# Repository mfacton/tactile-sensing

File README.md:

# Robotic Tactile Sensing with Soft Lattices

MIT Computer Science and Artificial Intelligence Laboratory

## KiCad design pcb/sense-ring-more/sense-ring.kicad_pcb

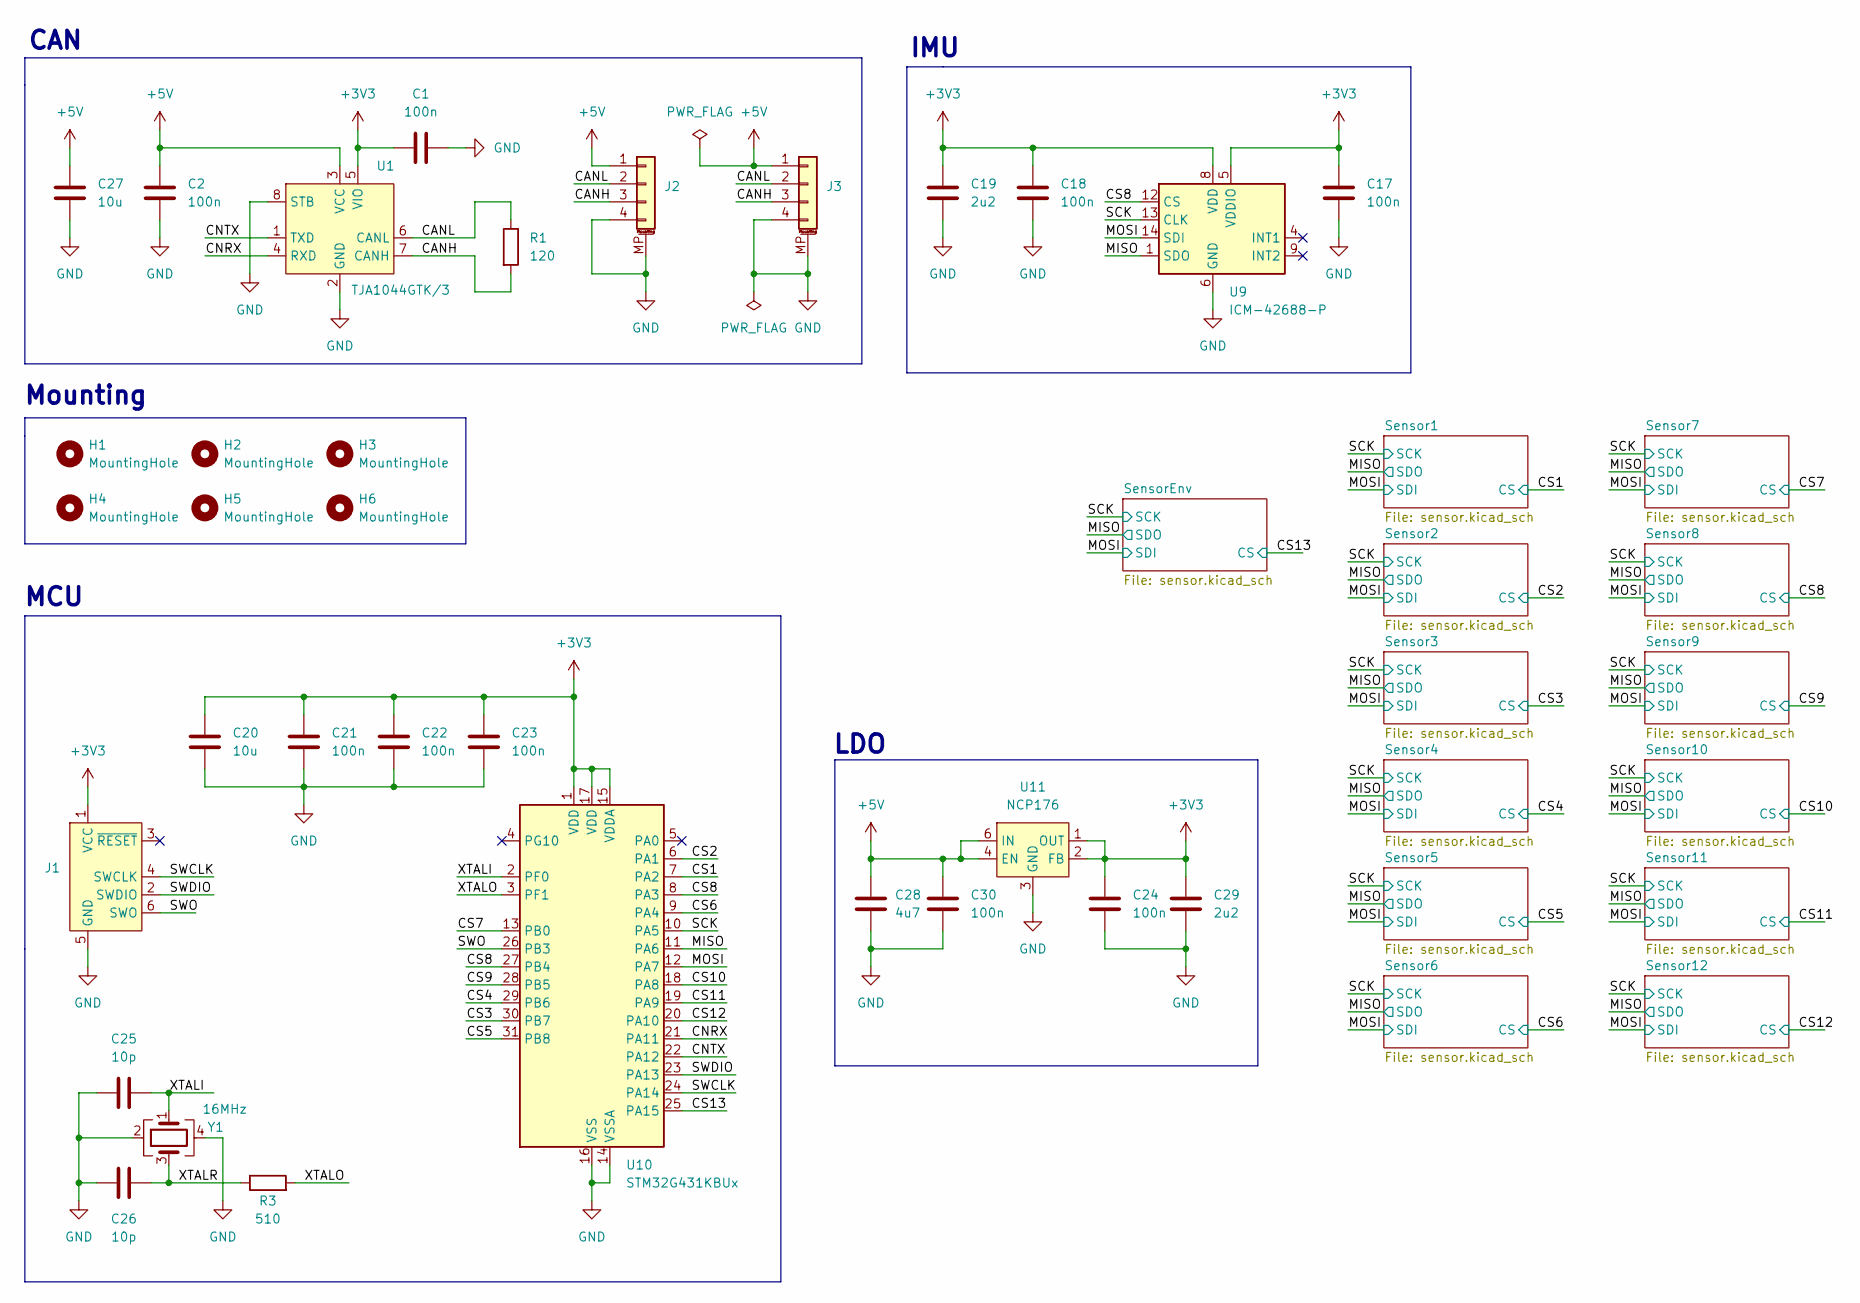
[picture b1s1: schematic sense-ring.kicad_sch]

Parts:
C1, C2, C17, C18, C21, C22, C23, C24, C30: 100n; C_0402_1005Metric; LCSC C1525
C19, C29: 2u2; C_0402_1005Metric; LCSC C12530
C20: 10u; C_0402_1005Metric; LCSC C15525
C25, C26: 10p; C_0402_1005Metric; LCSC C32949
C27: 10u; C_0603_1608Metric; LCSC C19702
C28: 4u7; C_0402_1005Metric; LCSC C23733
H1, H2, H3, H4, H5, H6: MountingHole; MountingHole_3.2mm_M3
J1: Conn_ARM_SWD_TagConnect_TC2030-NL; Tag-Connect_TC2030-IDC-NL_2x03_P1.27mm_Vertical
J2, J3: Conn_01x04_MountingPin; JST_SH_SM04B-SRSS-TB_1x04-1MP_P1.00mm_Horizontal; LCSC C160404
R1: 120; R_1206_3216Metric; LCSC C17909
R3: 510; R_0402_1005Metric; LCSC C25123
U1: TJA1044GTK/3; HVSON-8-1EP_3x3mm_P0.65mm_EP1.6x2.4mm; LCSC C2157795
U9: ICM-42688-P; LGA-14_3x2.5mm_P0.5mm_LayoutBorder3x4y; LCSC C1850418
U10: STM32G431KBUx; QFN-32-1EP_5x5mm_P0.5mm_EP3.45x3.45mm; LCSC C1341901
U11: NCP176; DFN-6-1EP_1.2x1.2mm_P0.4mm_EP0.3x0.94mm_PullBack; LCSC C233363
Y1: 16MHz; Crystal_SMD_3225-4Pin_3.2x2.5mm; LCSC C13738

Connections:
+3V3: C1.1, C17.1, C18.1, C19.1, C20.1, C21.1, C22.1, C23.1, C24.1, C29.1, J1.1 (VCC), U1.5 (VIO), U9.5 (VDDIO), U9.8 (VDD), U10.1 (VDD), U10.15 (VDDA), U10.17 (VDD), U11.1 (OUT), U11.2 (FB); also elsewhere on the board
+5V: C2.2, C27.1, C28.1, C30.1, J2.1, J3.1, U1.3 (VCC), U11.4 (EN), U11.6 (IN)
/CANH: J2.3, J3.3, R1.2, U1.7 (CANH)
/CANL: J2.2, J3.2, R1.1, U1.6 (CANL)
/CNRX: U1.4 (RXD), U10.21 (PA11)
/CNTX: U1.1 (TXD), U10.22 (PA12)
/CS1: U10.7 (PA2); also elsewhere on the board
/CS2: U10.6 (PA1); also elsewhere on the board
/CS3: U10.30 (PB7); also elsewhere on the board
/CS4: U10.29 (PB6); also elsewhere on the board
/CS5: U10.31 (PB8); also elsewhere on the board
/CS6: U10.9 (PA4); also elsewhere on the board
/CS7: U10.13 (PB0); also elsewhere on the board
/CS8: U9.12 (CS), U10.8 (PA3), U10.27 (PB4); also elsewhere on the board
/CS9: U10.28 (PB5); also elsewhere on the board
/CS10: U10.18 (PA8); also elsewhere on the board
/CS11: U10.19 (PA9); also elsewhere on the board
/CS12: U10.20 (PA10); also elsewhere on the board
/CS13: U10.25 (PA15); also elsewhere on the board
/MISO: U9.1 (SDO), U10.11 (PA6); also elsewhere on the board
/MOSI: U9.14 (SDI), U10.12 (PA7); also elsewhere on the board
/SCK: U9.13 (CLK), U10.10 (PA5); also elsewhere on the board
/SWCLK: J1.4 (SWCLK), U10.24 (PA14)
/SWDIO: J1.2 (SWDIO), U10.23 (PA13)
/SWO: J1.6 (SWO), U10.26 (PB3)
/XTALI: C25.2, U10.2 (PF0), Y1.1
/XTALO: R3.2, U10.3 (PF1)
/XTALR: C26.2, R3.1, Y1.3
GND: C1.2, C2.1, C17.2, C18.2, C19.2, C20.2, C21.2, C22.2, C23.2, C24.2, C25.1, C26.1, C27.2, C28.2, C29.2, C30.2, J1.5 (GND), J2.4, J2.MP (MountPin), J3.4, J3.MP (MountPin), U1.2 (GND), U1.8 (STB), U1.9 (EPAD), U9.6 (GND), U9.7 (RESV), U9.11 (RESV), U10.14 (VSSA), U10.16 (VSS), U10.32 (VSS), U10.33 (VSS), U11.3 (GND), U11.7 (EPAD), Y1.2, Y1.4; also elsewhere on the board

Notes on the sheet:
Mounting
LDO
MCU
CAN
IMU

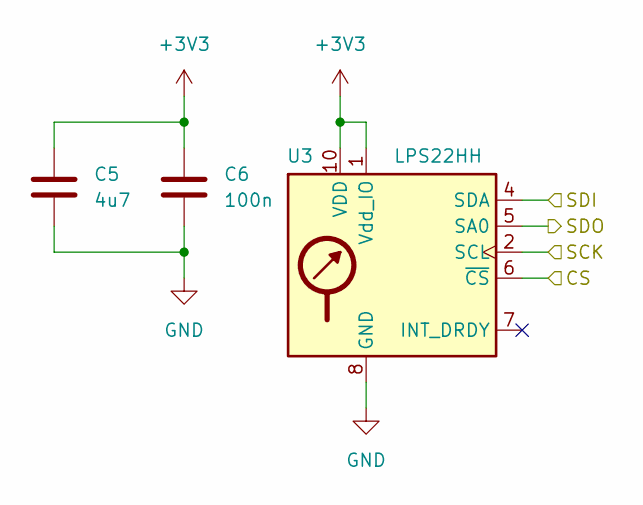
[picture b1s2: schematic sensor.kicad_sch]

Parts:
C5: 4u7; C_0402_1005Metric; LCSC C23733
C6: 100n; C_0402_1005Metric; LCSC C1525
U3: LPS22HH; ST_HLGA-10_2x2mm_P0.5mm_LayoutBorder3x2y; LCSC C2827824

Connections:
+3V3: C5.1, C6.1, U3.1 (Vdd_IO), U3.10 (VDD); also elsewhere on the board
/CS2: U3.6 (~CS); also elsewhere on the board
/MISO: U3.5 (SA0); also elsewhere on the board
/MOSI: U3.4 (SDA); also elsewhere on the board
/SCK: U3.2 (SCL); also elsewhere on the board
GND: C5.2, C6.2, U3.3 (GND), U3.8 (GND), U3.9 (GND); also elsewhere on the board

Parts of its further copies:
C3, C7, C9, C11, C13, C15, C31, C33, C35, C37, C39, C41: 4u7; C_0402_1005Metric; LCSC C23733
C4, C8, C10, C12, C14, C16, C32, C34, C36, C38, C40, C42: 100n; C_0402_1005Metric; LCSC C1525
U2, U4, U5, U6, U7, U8, U12, U13, U14, U15, U16, U17: LPS22HH; ST_HLGA-10_2x2mm_P0.5mm_LayoutBorder3x2y; LCSC C2827824

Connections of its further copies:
+3V3: C3.1, C4.1, C7.1, C8.1, C9.1, C10.1, C11.1, C12.1, C13.1, C14.1, C15.1, C16.1, C31.1, C32.1, C33.1, C34.1, C35.1, C36.1, C37.1, C38.1, C39.1, C40.1, C41.1, C42.1, U2.1 (Vdd_IO), U2.10 (VDD), U4.1 (Vdd_IO), U4.10 (VDD), U5.1 (Vdd_IO), U5.10 (VDD), U6.1 (Vdd_IO), U6.10 (VDD), U7.1 (Vdd_IO), U7.10 (VDD), U8.1 (Vdd_IO), U8.10 (VDD), U12.1 (Vdd_IO), U12.10 (VDD), U13.1 (Vdd_IO), U13.10 (VDD), U14.1 (Vdd_IO), U14.10 (VDD), U15.1 (Vdd_IO), U15.10 (VDD), U16.1 (Vdd_IO), U16.10 (VDD), U17.1 (Vdd_IO), U17.10 (VDD); also elsewhere on the board
/CS1: U2.6 (~CS); also elsewhere on the board
/CS3: U4.6 (~CS); also elsewhere on the board
/CS4: U5.6 (~CS); also elsewhere on the board
/CS5: U6.6 (~CS); also elsewhere on the board
/CS6: U8.6 (~CS); also elsewhere on the board
/CS7: U12.6 (~CS); also elsewhere on the board
/CS8: U13.6 (~CS); also elsewhere on the board
/CS9: U14.6 (~CS); also elsewhere on the board
/CS10: U15.6 (~CS); also elsewhere on the board
/CS11: U16.6 (~CS); also elsewhere on the board
/CS12: U17.6 (~CS); also elsewhere on the board
/CS13: U7.6 (~CS); also elsewhere on the board
/MISO: U2.5 (SA0), U4.5 (SA0), U5.5 (SA0), U6.5 (SA0), U7.5 (SA0), U8.5 (SA0), U12.5 (SA0), U13.5 (SA0), U14.5 (SA0), U15.5 (SA0), U16.5 (SA0), U17.5 (SA0); also elsewhere on the board
/MOSI: U2.4 (SDA), U4.4 (SDA), U5.4 (SDA), U6.4 (SDA), U7.4 (SDA), U8.4 (SDA), U12.4 (SDA), U13.4 (SDA), U14.4 (SDA), U15.4 (SDA), U16.4 (SDA), U17.4 (SDA); also elsewhere on the board
/SCK: U2.2 (SCL), U4.2 (SCL), U5.2 (SCL), U6.2 (SCL), U7.2 (SCL), U8.2 (SCL), U12.2 (SCL), U13.2 (SCL), U14.2 (SCL), U15.2 (SCL), U16.2 (SCL), U17.2 (SCL); also elsewhere on the board
GND: C3.2, C4.2, C7.2, C8.2, C9.2, C10.2, C11.2, C12.2, C13.2, C14.2, C15.2, C16.2, C31.2, C32.2, C33.2, C34.2, C35.2, C36.2, C37.2, C38.2, C39.2, C40.2, C41.2, C42.2, U2.3 (GND), U2.8 (GND), U2.9 (GND), U4.3 (GND), U4.8 (GND), U4.9 (GND), U5.3 (GND), U5.8 (GND), U5.9 (GND), U6.3 (GND), U6.8 (GND), U6.9 (GND), U7.3 (GND), U7.8 (GND), U7.9 (GND), U8.3 (GND), U8.8 (GND), U8.9 (GND), U12.3 (GND), U12.8 (GND), U12.9 (GND), U13.3 (GND), U13.8 (GND), U13.9 (GND), U14.3 (GND), U14.8 (GND), U14.9 (GND), U15.3 (GND), U15.8 (GND), U15.9 (GND), U16.3 (GND), U16.8 (GND), U16.9 (GND), U17.3 (GND), U17.8 (GND), U17.9 (GND); also elsewhere on the board

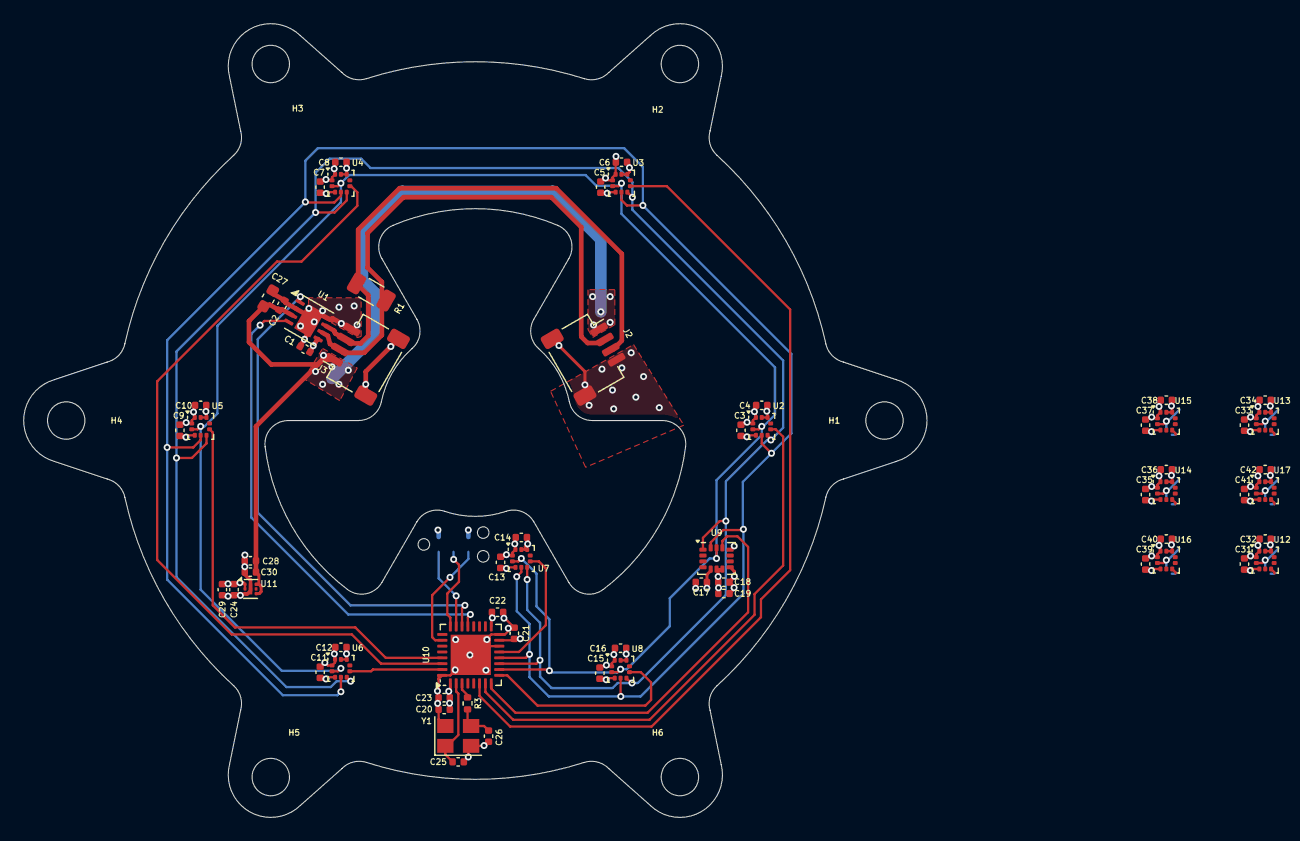
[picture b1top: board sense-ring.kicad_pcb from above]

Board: 4 copper layers, 77.3 x 67.9 mm, 71 parts (1 on the bottom side), 29 nets.

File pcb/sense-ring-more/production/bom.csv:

Designator,Footprint,Quantity,Value,LCSC Part #
"C1, C10, C12, C14, C16, C17, C18, C2, C21, C22, C23, C24, C30, C4, C6, C8",0402,16,100n,C1525
"C11, C13, C15, C28, C3, C5, C7, C9",0402,8,4u7,C23733
"C19, C29",0402,2,2u2,C12530
C20,0402,1,10u,C15525
"C25, C26",0402,2,10p,C32949
C27,0603,1,10u,C19702
"J2, J3",JST_SH_SM04B-SRSS-TB_1x04-1MP_P1.00mm_Horizontal,2,Conn_01x04_MountingPin,C160404
R1,1206,1,120,C17909
R3,0402,1,510,C25123
U1,HVSON-8-1EP_3x3mm_P0.65mm_EP1.6x2.4mm,1,TJA1044GTK/3,C2157795
U10,QFN-32-1EP_5x5mm_P0.5mm_EP3.45x3.45mm,1,STM32G431KBUx,C1341901
U11,DFN-6-1EP_1.2x1.2mm_P0.4mm_EP0.3x0.94mm_PullBack,1,NCP176,C233363
"U2, U3, U4, U5, U6, U7, U8",ST_HLGA-10_2x2mm_P0.5mm_LayoutBorder3x2y,7,LPS22HH,C2827824
U9,LGA-14_3x2.5mm_P0.5mm_LayoutBorder3x4y,1,ICM-42688-P,C1850418
Y1,Crystal_SMD_3225-4Pin_3.2x2.5mm,1,16MHz,C13738

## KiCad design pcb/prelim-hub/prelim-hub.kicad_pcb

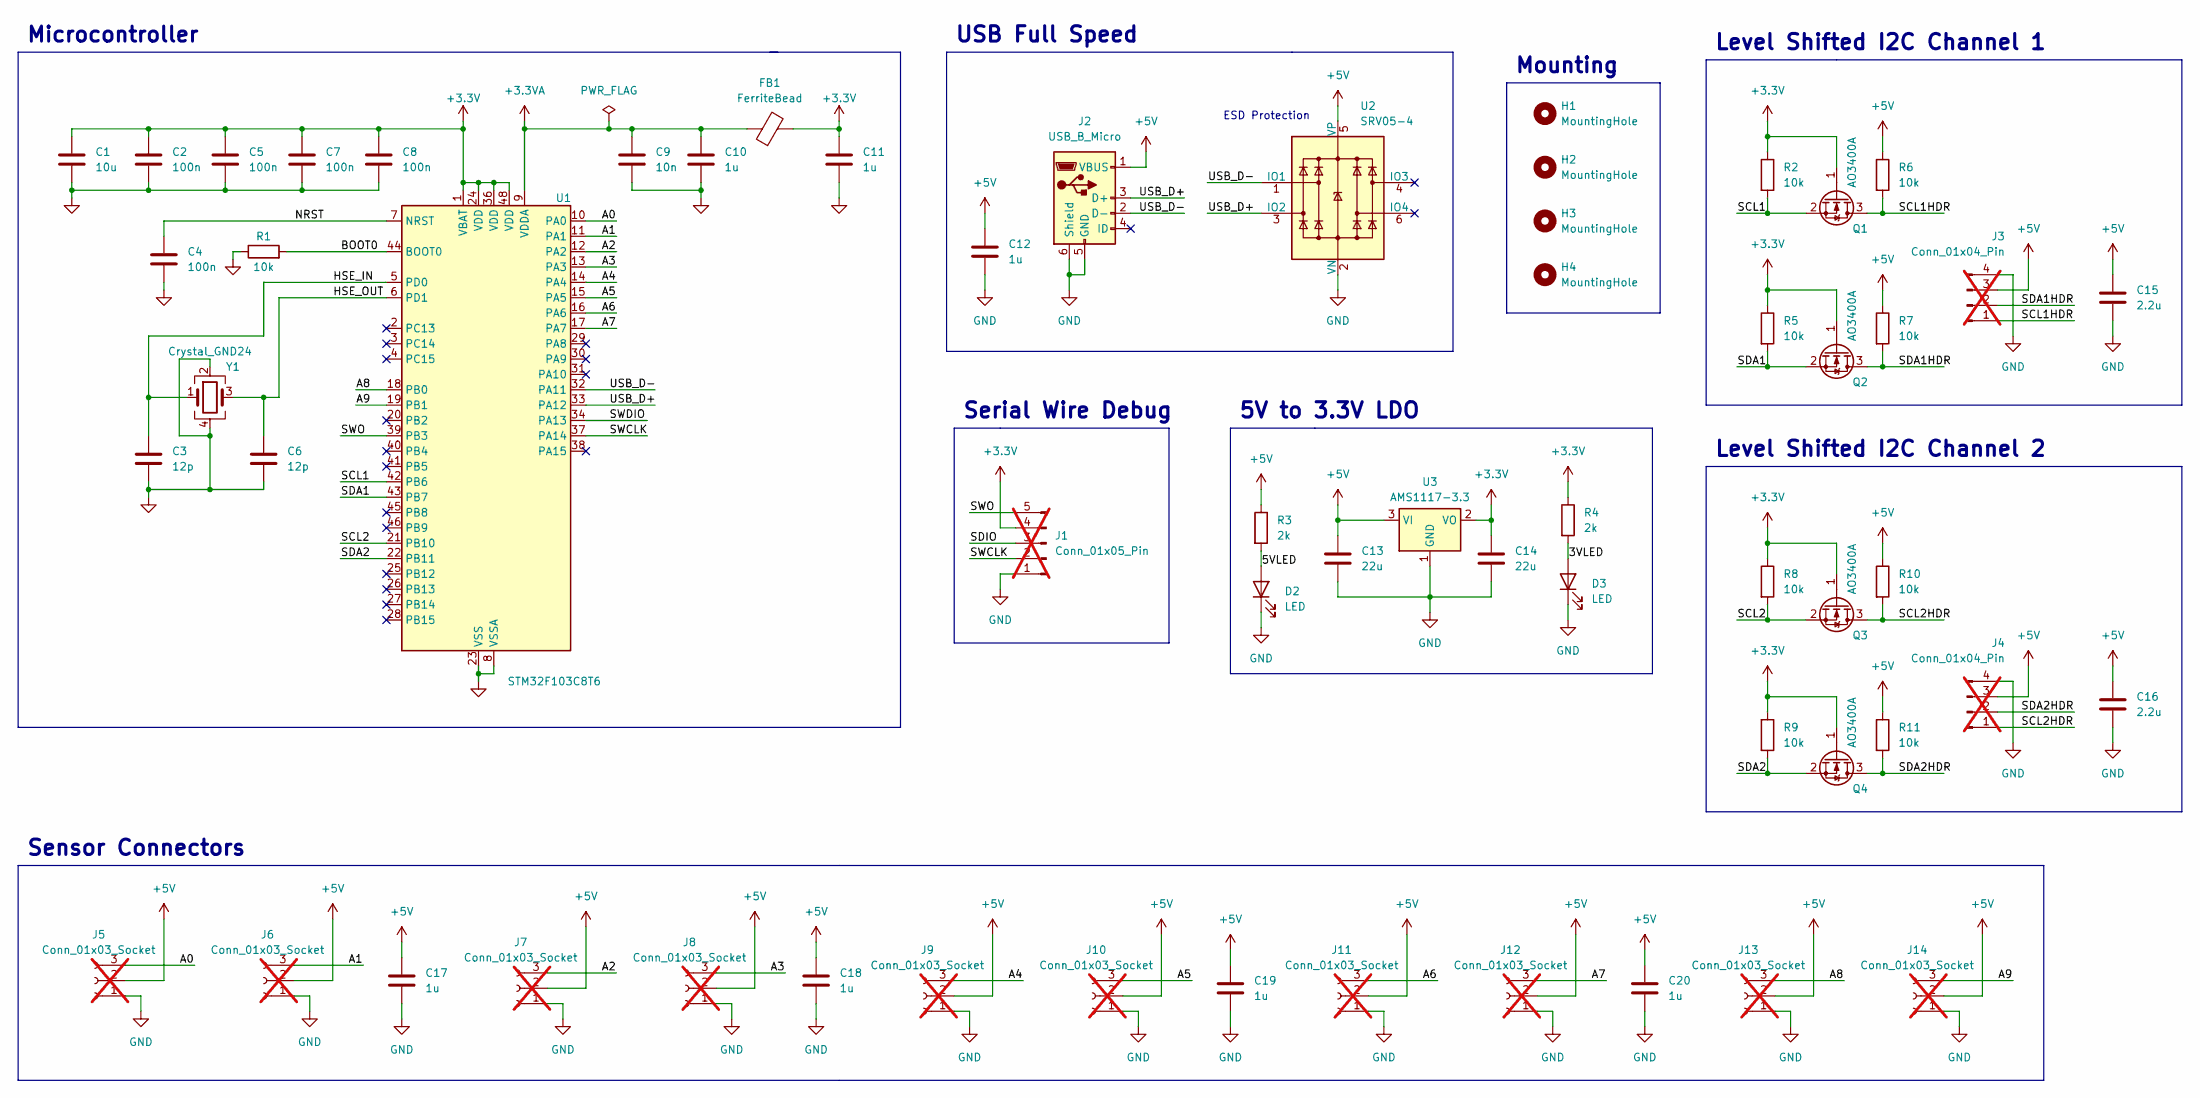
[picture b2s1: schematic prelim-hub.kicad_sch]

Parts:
C1: 10u; C_0603_1608Metric
C2, C4, C5, C7, C8: 100n; C_0402_1005Metric
C3, C6: 12p; C_0402_1005Metric
C9: 10n; C_0402_1005Metric
C10, C11, C12, C17, C18, C19, C20: 1u; C_0402_1005Metric
C13, C14: 22u; C_0805_2012Metric
C15, C16: 2.2u; C_0603_1608Metric
D2, D3: LED; LED_0603_1608Metric
FB1: FerriteBead; L_0805_2012Metric
H1, H2, H3, H4: MountingHole; MountingHole_3.2mm_M3
J1: Conn_01x05_Pin; Conn_Header_P5-2.54; not fitted
J2: USB_B_Micro; USB_Micro-B_Molex-105017-0001
J3, J4: Conn_01x04_Pin; Conn_JST_P4-2.54mm; not fitted
J5, J6, J7, J8, J9, J10, J11, J12, J13, J14: Conn_01x03_Socket; Conn_JST_P3-2.54; not fitted
Q1, Q2, Q3, Q4: AO3400A; SOT-23
R1, R2, R5, R6, R7, R8, R9, R10, R11: 10k; R_0402_1005Metric
R3, R4: 2k; R_0402_1005Metric
U1: STM32F103C8T6; LQFP-48_7x7mm_P0.5mm; LCSC C8734
U2: SRV05-4; SOT-23-6; LCSC C7420376
U3: AMS1117-3.3; SOT-223-3_TabPin2
Y1: Crystal_GND24; Crystal_SMD_3225-4Pin_3.2x2.5mm; LCSC C13738

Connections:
+3.3V: C1.1, C2.1, C5.1, C7.1, C8.1, C11.1, C14.1, FB1.2, J1.4, Q1.1 (G), Q2.1 (G), Q3.1 (G), Q4.1 (G), R2.1, R4.1, R5.1, R8.1, R9.1, U1.1 (VBAT), U1.24 (VDD), U1.36 (VDD), U1.48 (VDD), U3.2 (VO)
+3.3VA: C9.1, C10.1, FB1.1, U1.9 (VDDA)
+5V: C12.1, C13.1, C15.1, C16.1, C17.1, C18.1, C19.1, C20.1, J2.1 (VBUS), J3.3, J4.3, J5.2, J6.2, J7.2, J8.2, J9.2, J10.2, J11.2, J12.2, J13.2, J14.2, R3.1, R6.1, R7.1, R10.1, R11.1, U2.5 (VP), U3.3 (VI)
/3VLED: D3.2 (A), R4.2
/5VLED: D2.2 (A), R3.2
/A0: J5.3, U1.10 (PA0)
/A1: J6.3, U1.11 (PA1)
/A2: J7.3, U1.12 (PA2)
/A3: J8.3, U1.13 (PA3)
/A4: J9.3, U1.14 (PA4)
/A5: J10.3, U1.15 (PA5)
/A6: J11.3, U1.16 (PA6)
/A7: J12.3, U1.17 (PA7)
/A8: J13.3, U1.18 (PB0)
/A9: J14.3, U1.19 (PB1)
/BOOT0: R1.2, U1.44 (BOOT0)
/HSE_IN: C3.1, U1.5 (PD0), Y1.1
/HSE_OUT: C6.1, U1.6 (PD1), Y1.3
/NRST: C4.1, U1.7 (NRST)
/SCL1: Q1.2 (S), R2.2, U1.42 (PB6)
/SCL1HDR: J3.1, Q1.3 (D), R6.2
/SCL2: Q3.2 (S), R8.2, U1.21 (PB10)
/SCL2HDR: J4.1, Q3.3 (D), R10.2
/SDA1: Q2.2 (S), R5.2, U1.43 (PB7)
/SDA1HDR: J3.2, Q2.3 (D), R7.2
/SDA2: Q4.2 (S), R9.2, U1.22 (PB11)
/SDA2HDR: J4.2, Q4.3 (D), R11.2
/SDIO: J1.3
/SWCLK: J1.2, U1.37 (PA14)
/SWDIO: U1.34 (PA13)
/SWO: J1.5, U1.39 (PB3)
/USB_D+: J2.3 (D+), U1.33 (PA12), U2.3 (IO2)
/USB_D-: J2.2 (D-), U1.32 (PA11), U2.1 (IO1)
GND: C1.2, C2.2, C3.2, C4.2, C5.2, C6.2, C7.2, C8.2, C9.2, C10.2, C11.2, C12.2, C13.2, C14.2, C15.2, C16.2, C17.2, C18.2, C19.2, C20.2, D2.1 (K), D3.1 (K), J1.1, J2.5 (GND), J2.6 (Shield), J3.4, J4.4, J5.1, J6.1, J7.1, J8.1, J9.1, J10.1, J11.1, J12.1, J13.1, J14.1, R1.1, U1.8 (VSSA), U1.23 (VSS), U1.35 (VSS), U1.47 (VSS), U2.2 (VN), U3.1 (GND), Y1.2, Y1.4

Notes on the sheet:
Mounting
Level Shifted I2C Channel 1
Microcontroller
5V to 3.3V LDO
Sensor Connectors
USB Full Speed
ESD Protection
Serial Wire Debug
Level Shifted I2C Channel 2

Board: 2 copper layers, 60 parts (0 on the bottom side), 32 nets, no tracks yet.

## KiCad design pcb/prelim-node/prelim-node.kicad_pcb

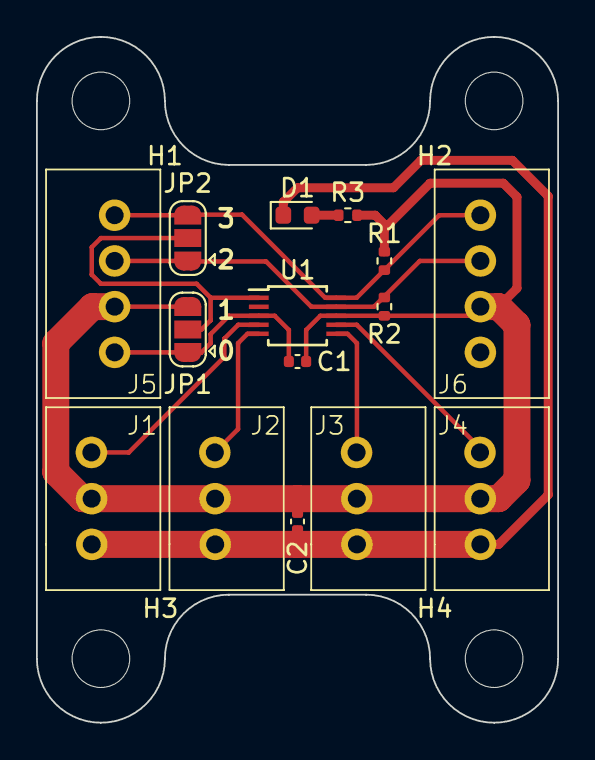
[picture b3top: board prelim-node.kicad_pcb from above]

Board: 2 copper layers, 29.0 x 38.1 mm, 19 parts (0 on the bottom side), 10 nets.

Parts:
C1: 100n; C_0402_1005Metric
C2: 1u; C_0402_1005Metric
D1: LED; LED_0603_1608Metric
H1, H2, H3, H4: MountingHole; MountingHole_3.2mm_M3
J1, J2, J3, J4: Conn_01x03_Socket; Conn_JST_P3-2.54
J5, J6: Conn_01x04_Pin; Conn_JST_P4-2.54mm
JP1, JP2: SolderJumper_3_Open; SolderJumper-3_P1.3mm_Open_RoundedPad1.0x1.5mm
R1, R2: 10k; R_0402_1005Metric
R3: 2k; R_0402_1005Metric
U1: ADS1115IDGS; TSSOP-10_3x3mm_P0.5mm

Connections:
+5V: C1.1, C2.1, J1.2, J2.2, J3.2, J4.2, J5.3, J6.2, JP1.3 (B), R1.1, R2.1, R3.1, U1.8 (VDD)
/5VLED: D1.2 (A), R3.2
/A1: J1.3, U1.4 (AIN0)
/A2: J2.3, U1.5 (AIN1)
/A3: J3.3, U1.6 (AIN2)
/A4: J4.3, U1.7 (AIN3)
/ADDR: JP1.2 (C), JP2.2 (C), U1.1 (ADDR)
/SCL: J5.1, J6.4, JP2.3 (B), R1.2, U1.10 (SCL)
/SDA: J5.2, J6.3, JP2.1 (A), R2.2, U1.9 (SDA)
GND: C1.2, C2.2, D1.1 (K), J1.1, J2.1, J3.1, J4.1, J5.4, J6.1, JP1.1 (A), U1.3 (GND)

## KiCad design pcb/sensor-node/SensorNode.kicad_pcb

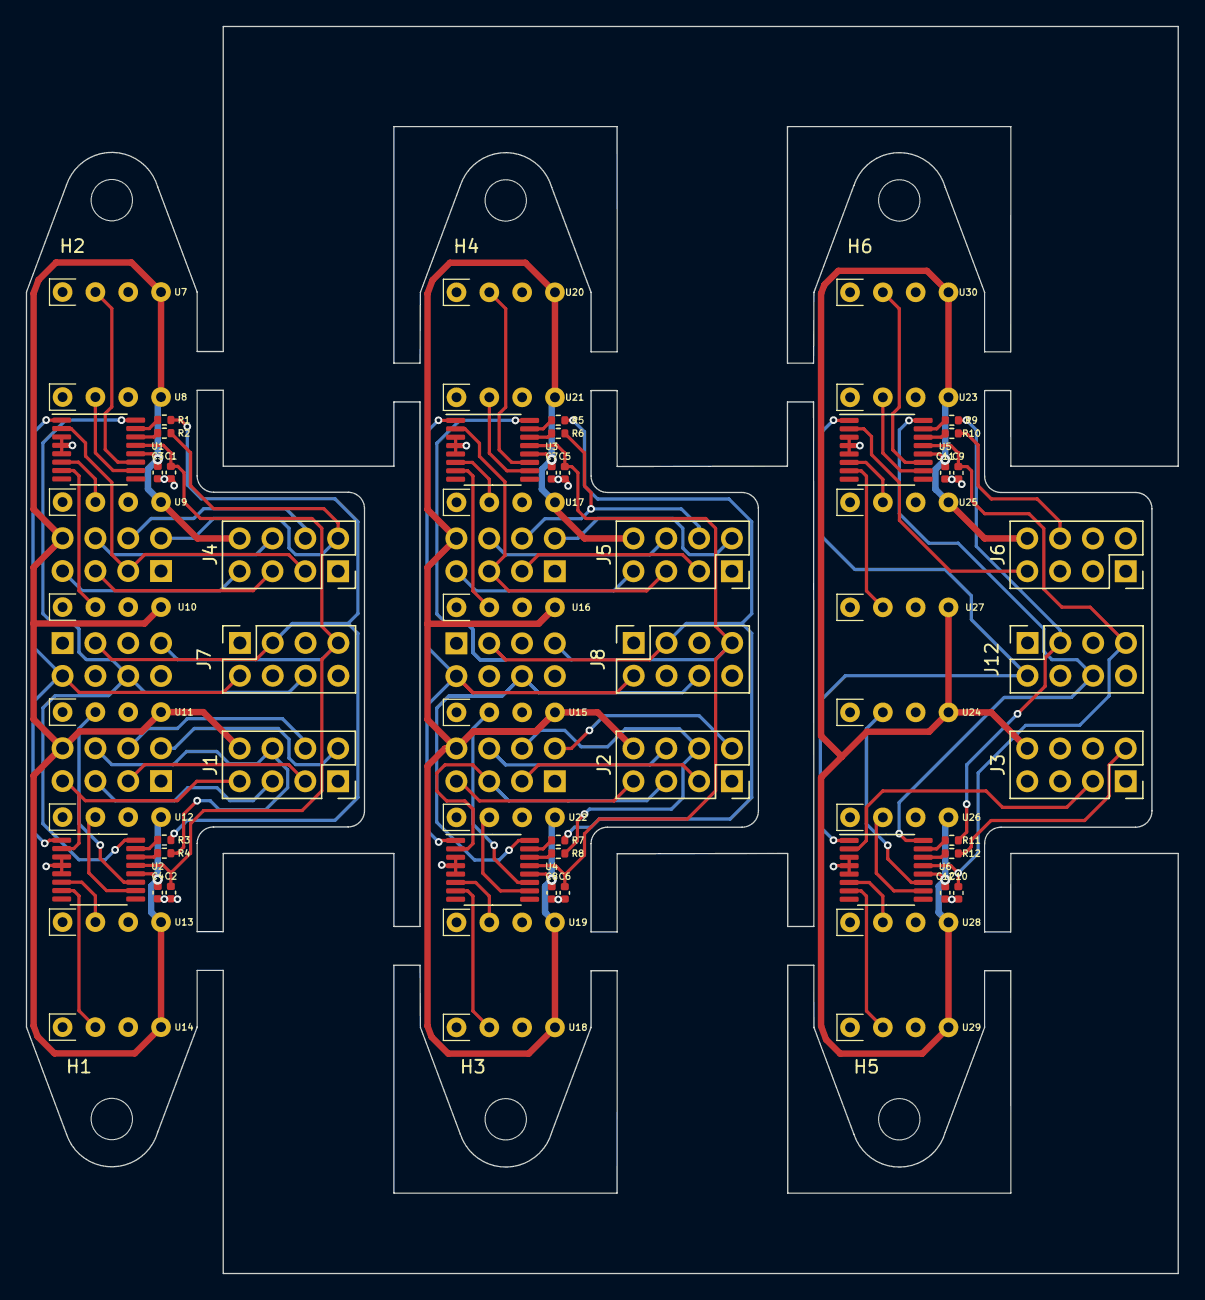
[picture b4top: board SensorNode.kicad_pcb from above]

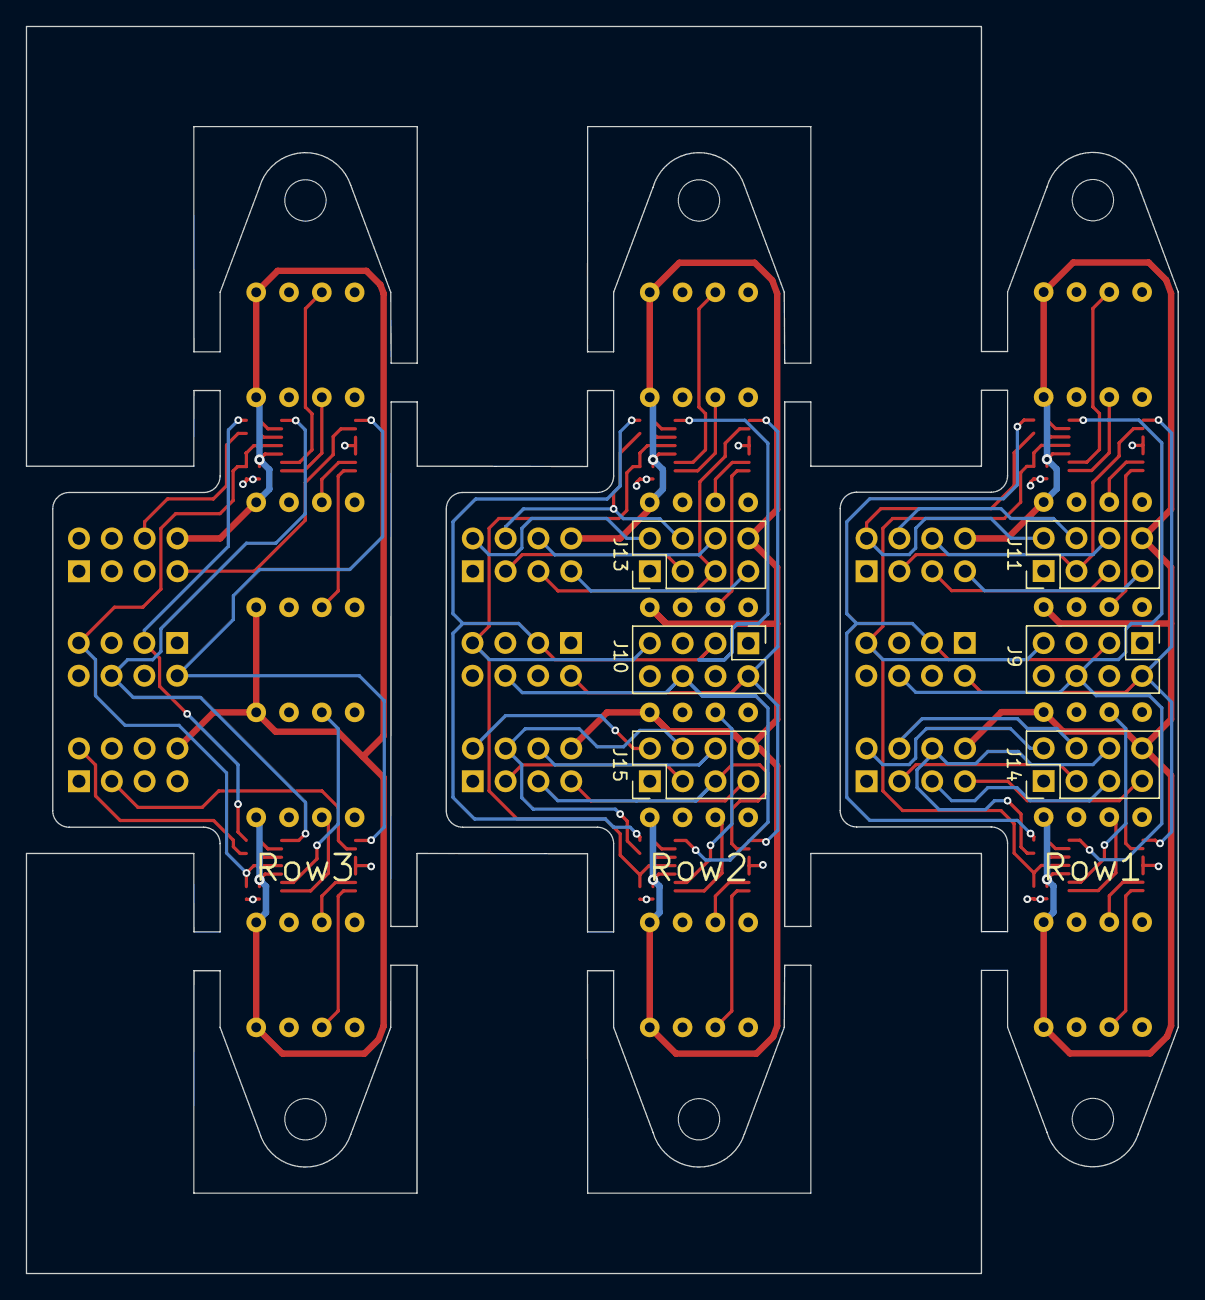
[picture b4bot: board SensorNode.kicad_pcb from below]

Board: 4 copper layers, 89.1 x 96.5 mm, 75 parts (6 on the bottom side), 76 nets.

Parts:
C1, C2, C3, C4, C5, C6, C7, C8, C9, C10, C11, C12: 100n; C_0402_1005Metric
H1, H2, H3, H4, H5, H6: MountingHole; MountingHole_3.2mm_M3
J1, J2, J3, J4, J5, J6, J7, J8, J12: Conn_02x04_Odd_Even; PinSocket_2x04_P2.54mm_Vertical
J9, J10, J11, J13, J14, J15: Conn_02x04_Odd_Even; PinHeader_2x04_P2.54mm_Vertical
R1, R2, R3, R4, R5, R6, R7, R8, R9, R10, R11, R12: 22; R_0402_1005Metric
U1, U2, U3, U4, U5, U6: ADS1220xPW; TSSOP-16_4.4x5mm_P0.65mm
U7, U8, U9, U10, U11, U12, U13, U14, U15, U16, U17, U18, U19, U20, U21, U22, U23, U24, U25, U26, U27, U28, U29, U30: P4V-MINI

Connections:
+3.3V: C1.1, C2.1, C5.1, C6.1, C9.1, C10.1, J7.7, J8.7, J9.7, J10.7, J12.7, U1.13 (DVDD), U2.13 (DVDD), U3.13 (DVDD), U4.13 (DVDD), U5.13 (DVDD), U6.13 (DVDD)
+5V: C3.1, C4.1, C7.1, C8.1, C11.1, C12.1, J1.8, J2.8, J3.8, J4.8, J5.8, J6.8, J11.8, J13.8, J14.8, J15.8, U1.12 (AVDD), U2.12 (AVDD), U3.12 (AVDD), U4.12 (AVDD), U5.12 (AVDD), U6.12 (AVDD), U7.1 (VCC), U8.1 (VCC), U9.1 (VCC), U10.1 (VCC), U11.1 (VCC), U12.1 (VCC), U13.1 (VCC), U14.1 (VCC), U15.1 (VCC), U16.1 (VCC), U17.1 (VCC), U18.1 (VCC), U19.1 (VCC), U20.1 (VCC), U21.1 (VCC), U22.1 (VCC), U23.1 (VCC), U24.1 (VCC), U25.1 (VCC), U26.1 (VCC), U27.1 (VCC), U28.1 (VCC), U29.1 (VCC), U30.1 (VCC)
/CSA1: J4.3, J11.3, U1.2 (~CS)
/CSA2: J4.5, J11.5
/CSA3: J4.7, J11.7
/CSA4: J1.3, J14.3
/CSA5: J1.5, J14.5
/CSA6: J1.7, J14.7, U2.2 (~CS)
/CSB1: J5.3, J13.3
/CSB2: J5.5, J13.5, U3.2 (~CS)
/CSB3: J5.7, J13.7
/CSB4: J2.3, J15.3
/CSB5: J2.5, J15.5, U4.2 (~CS)
/CSB6: J2.7, J15.7
/CSC3: J6.7, U5.2 (~CS)
/CSC4: J3.3, U6.2 (~CS)
/ConnectorIn1/MISO: J7.3, J9.3, R1.2, R3.2
/ConnectorIn1/MOSI: J7.6, J9.6, U1.16 (DIN), U2.16 (DIN)
/ConnectorIn1/SCK: J7.2, J9.2, U1.1 (SCLK), U2.1 (SCLK)
/ConnectorIn2/MISO: J8.3, J10.3, R5.2, R7.2
/ConnectorIn2/MOSI: J8.6, J10.6, U3.16 (DIN), U4.16 (DIN)
/ConnectorIn2/SCK: J8.2, J10.2, U3.1 (SCLK), U4.1 (SCLK)
/ConnectorIn3/MISO: J12.3, R9.2, R11.2
/ConnectorIn3/MOSI: J12.6, U5.16 (DIN), U6.16 (DIN)
/ConnectorIn3/SCK: J12.2, U5.1 (SCLK), U6.1 (SCLK)
/DRA1: J4.2, J11.2, R2.2
/DRA2: J4.4, J11.4
/DRA3: J4.6, J11.6
/DRA4: J1.2, J14.2
/DRA5: J1.4, J14.4
/DRA6: J1.6, J14.6, R4.2
/DRB1: J5.2, J13.2
/DRB2: J5.4, J13.4, R6.2
/DRB3: J5.6, J13.6
/DRB4: J2.2, J15.2
/DRB5: J2.4, J15.4, R8.2
/DRB6: J2.6, J15.6
/DRC3: J6.6, R10.2
/DRC4: J3.2, R12.2
/SensorRow1/SNS1: U1.11 (AIN0/REFP1), U7.3 (REF)
/SensorRow1/SNS2: U1.10 (AIN1), U8.3 (REF)
/SensorRow1/SNS3: U1.6 (AIN3/REFN1), U9.3 (REF)
/SensorRow1/SNS4: U1.7 (AIN2), U10.3 (REF)
/SensorRow1/SNS5: U2.11 (AIN0/REFP1), U11.3 (REF)
/SensorRow1/SNS6: U2.10 (AIN1), U12.3 (REF)
/SensorRow1/SNS7: U2.6 (AIN3/REFN1), U13.3 (REF)
/SensorRow1/SNS8: U2.7 (AIN2), U14.3 (REF)
/SensorRow2/SNS1: U3.11 (AIN0/REFP1), U20.3 (REF)
/SensorRow2/SNS2: U3.10 (AIN1), U21.3 (REF)
/SensorRow2/SNS3: U3.6 (AIN3/REFN1), U17.3 (REF)
/SensorRow2/SNS4: U3.7 (AIN2), U16.3 (REF)
/SensorRow2/SNS5: U4.11 (AIN0/REFP1), U15.3 (REF)
/SensorRow2/SNS6: U4.10 (AIN1), U22.3 (REF)
/SensorRow2/SNS7: U4.6 (AIN3/REFN1), U19.3 (REF)
/SensorRow2/SNS8: U4.7 (AIN2), U18.3 (REF)
/SensorRow3/SNS1: U5.11 (AIN0/REFP1), U30.3 (REF)
/SensorRow3/SNS2: U5.10 (AIN1), U23.3 (REF)
/SensorRow3/SNS3: U5.6 (AIN3/REFN1), U25.3 (REF)
/SensorRow3/SNS4: U5.7 (AIN2), U27.3 (REF)
/SensorRow3/SNS5: U6.11 (AIN0/REFP1), U24.3 (REF)
/SensorRow3/SNS6: U6.10 (AIN1), U26.3 (REF)
/SensorRow3/SNS7: U6.6 (AIN3/REFN1), U28.3 (REF)
/SensorRow3/SNS8: U6.7 (AIN2), U29.3 (REF)
GND: C1.2, C2.2, C3.2, C4.2, C5.2, C6.2, C7.2, C8.2, C9.2, C10.2, C11.2, C12.2, J1.1, J2.1, J3.1, J4.1, J5.1, J6.1, J7.1, J7.4, J7.5, J7.8, J8.1, J8.4, J8.5, J8.8, J9.1, J9.4, J9.5, J9.8, J10.1, J10.4, J10.5, J10.8, J11.1, J12.1, J12.4, J12.5, J12.8, J13.1, J14.1, J15.1, U1.3 (CLK), U1.4 (DGND), U1.5 (AVSS), U2.3 (CLK), U2.4 (DGND), U2.5 (AVSS), U3.3 (CLK), U3.4 (DGND), U3.5 (AVSS), U4.3 (CLK), U4.4 (DGND), U4.5 (AVSS), U5.3 (CLK), U5.4 (DGND), U5.5 (AVSS), U6.3 (CLK), U6.4 (DGND), U6.5 (AVSS), U7.2 (GND), U8.2 (GND), U9.2 (GND), U10.2 (GND), U11.2 (GND), U12.2 (GND), U13.2 (GND), U14.2 (GND), U15.2 (GND), U16.2 (GND), U17.2 (GND), U18.2 (GND), U19.2 (GND), U20.2 (GND), U21.2 (GND), U22.2 (GND), U23.2 (GND), U24.2 (GND), U25.2 (GND), U26.2 (GND), U27.2 (GND), U28.2 (GND), U29.2 (GND), U30.2 (GND)
unnamed: R1.1, U1.15 (DOUT/~DRDY)
unnamed: R2.1, U1.14 (~DRDY)
unnamed: R3.1, U2.15 (DOUT/~DRDY)
unnamed: R4.1, U2.14 (~DRDY)
unnamed: R5.1, U3.15 (DOUT/~DRDY)
unnamed: R6.1, U3.14 (~DRDY)
unnamed: R7.1, U4.15 (DOUT/~DRDY)
unnamed: R8.1, U4.14 (~DRDY)
unnamed: R9.1, U5.15 (DOUT/~DRDY)
unnamed: R10.1, U5.14 (~DRDY)
unnamed: R11.1, U6.15 (DOUT/~DRDY)
unnamed: R12.1, U6.14 (~DRDY)

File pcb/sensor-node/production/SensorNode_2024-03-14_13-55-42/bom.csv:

Designator,Footprint,Quantity,Value,LCSC Part #
"C1, C10, C11, C12, C2, C3, C4, C5, C6, C7, C8, C9",0402,12,100n,
"J1, J12, J2, J3, J4, J5, J6, J7, J8",PinSocket_2x04_P2.54mm_Vertical,9,Conn_02x04_Odd_Even,
"J10, J11, J13, J14, J15, J9",PinHeader_2x04_P2.54mm_Vertical,6,Conn_02x04_Odd_Even,
"R1, R10, R11, R12, R2, R3, R4, R5, R6, R7, R8, R9",0402,12,22,
"U1, U3, U5",TSSOP-16_4.4x5mm_P0.65mm,3,ADS1220xPW,C48263
"U2, U4, U6",TSSOP-16_4.4x5mm_P0.65mm,3,ADS1220xPW,
